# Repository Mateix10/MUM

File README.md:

# MUM
Matt's Universal Macropad (MUM) is a 7-key macropad. It uses the kmk frimware.
# Features
- 7 programable keys
- 2 rgb leds
# CAD Model
It has 2 seperate 3d-printed pieces. The bottom case where the PCB goes, and the top cover.

Made in Fusion 360.
# PCB
The PCB was made in KiCad.

Schematic

PCB

# Frimware
This macropad uses KMK

The code is written in python and it is where you can configure the macros.

The Frimware/main.py code has the following macros:
- First row of keys (the two far away from eachother) are volume controls: the left one is vol. up, and the other vol. down.
- The second row is playback control. Left is Backwords, middle is Play/Pause, right is Forwards.
- The third, and last row is copy paste. Left is Copy, and Right is Paste.

# BOM
Here's everything you need to bring this hackpad to life!

- 4x Cherry MX Switches
- 2x SK6812 MINI Leds
- 1x XIAO RP2040
- 4x Blank DSA Keycaps
- 4x M3x16 Bolt
- 4x M3 Heatset

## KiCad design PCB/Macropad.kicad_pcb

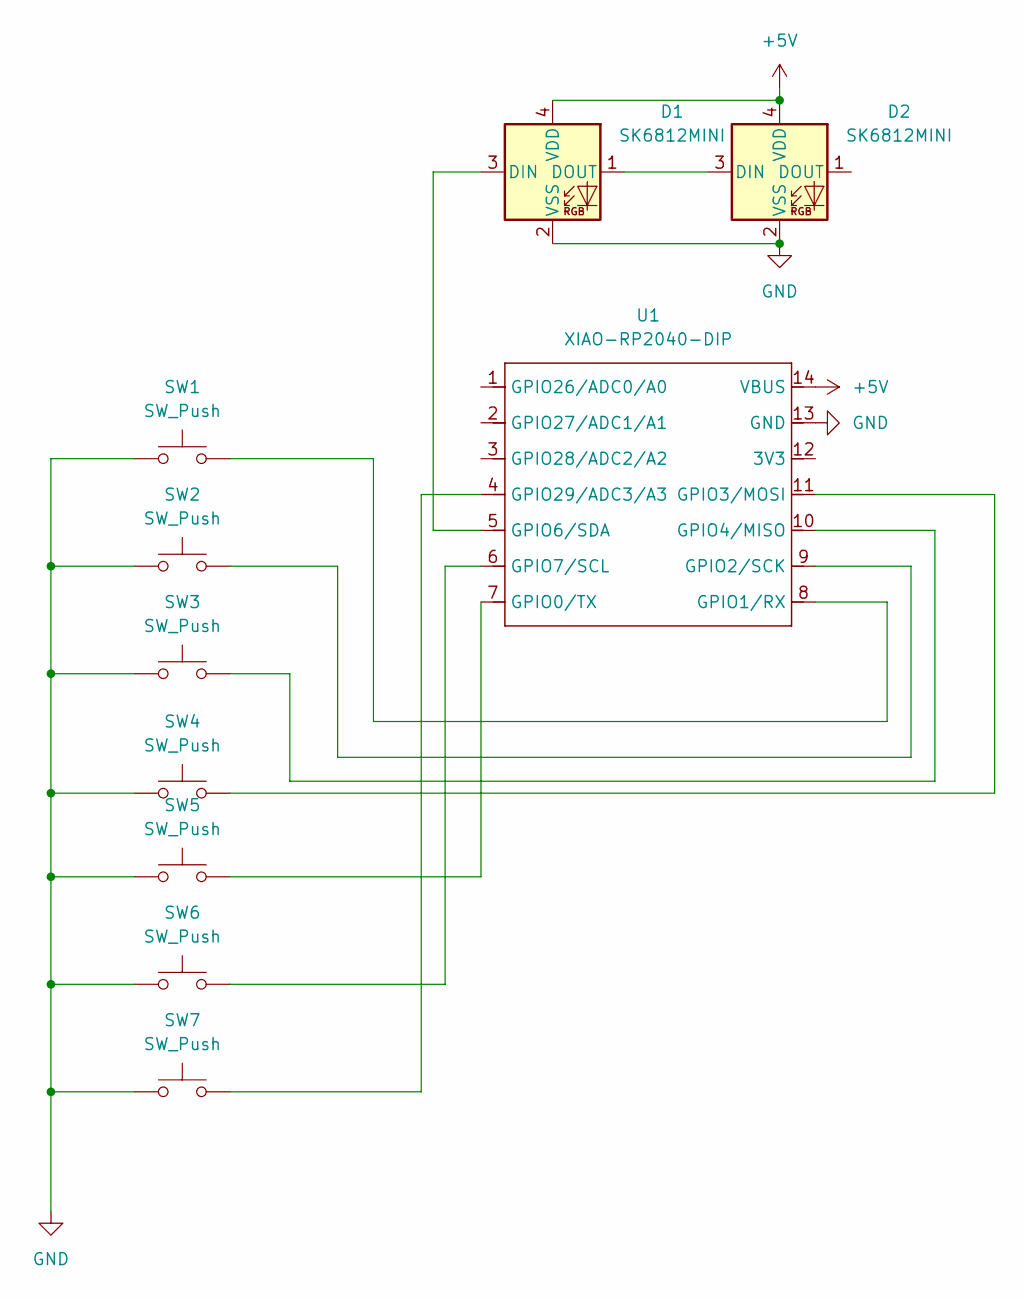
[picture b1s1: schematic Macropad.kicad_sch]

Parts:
D1, D2: SK6812MINI; LED_SK6812MINI_PLCC4_3.5x3.5mm_P1.75mm
SW1, SW2, SW3, SW4, SW5, SW6, SW7: SW_Push; SW_Cherry_MX_1.00u_PCB
U1: XIAO-RP2040-DIP

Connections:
+5V: D1.4 (VDD), D2.4 (VDD), U1.14 (VBUS)
GND: D1.2 (VSS), D2.2 (VSS), SW1.1, SW2.1, SW3.1, SW4.1, SW5.1, SW6.1, SW7.1, U1.13 (GND)
unnamed: D1.3 (DIN), U1.5 (GPIO6/SDA)
unnamed: D1.1 (DOUT), D2.3 (DIN)
unnamed: SW5.2, U1.7 (GPIO0/TX)
unnamed: SW1.2, U1.8 (GPIO1/RX)
unnamed: SW2.2, U1.9 (GPIO2/SCK)
unnamed: SW4.2, U1.11 (GPIO3/MOSI)
unnamed: SW3.2, U1.10 (GPIO4/MISO)
unnamed: SW6.2, U1.6 (GPIO7/SCL)
unnamed: SW7.2, U1.4 (GPIO29/ADC3/A3)

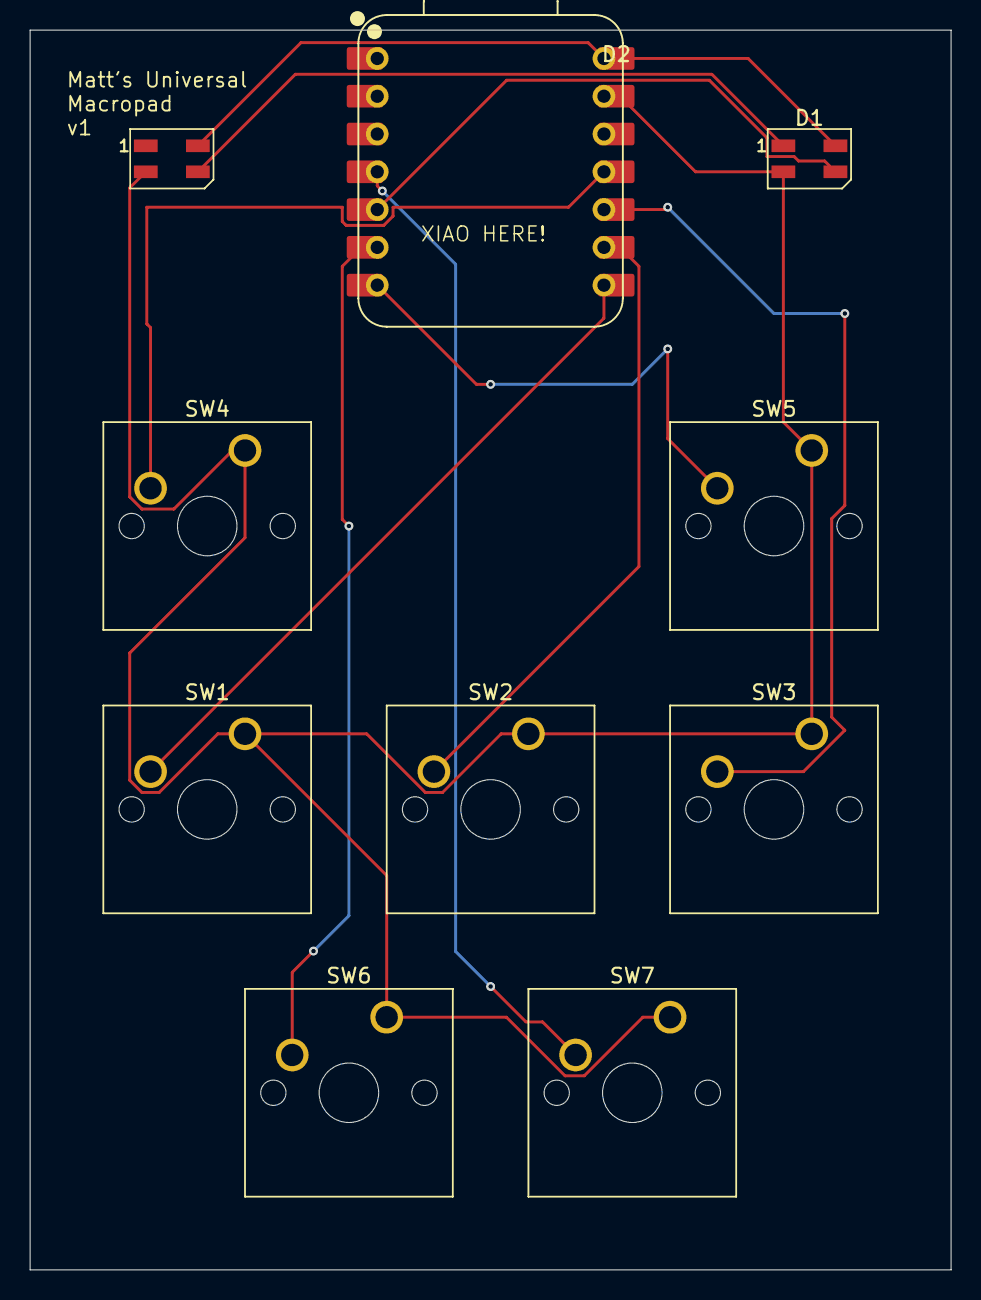
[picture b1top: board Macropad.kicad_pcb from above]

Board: 2 copper layers, 61.9 x 83.3 mm, 10 parts (0 on the bottom side), 11 nets.

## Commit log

2025-12-07 Enhance README with project details and features
    Added project description and features section to README.
2025-12-07 Add project files
2025-12-07 Remove tracked .DS_Store files
2025-12-07 Add .gitignore and exclude .DS_Store files
2025-12-07 Update README to include code and macro details
    Added a section about the code and macro configuration.
2025-12-07 Add example.py
2025-12-08 Redo folder structure
